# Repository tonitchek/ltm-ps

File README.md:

ltm-ps
======
Power Supply board based on Linear Technology uModule (LTM).

Contents
========
circuit_board :containing the design of the PCB.
simu          :simulation of the design based on LTSpiceIV

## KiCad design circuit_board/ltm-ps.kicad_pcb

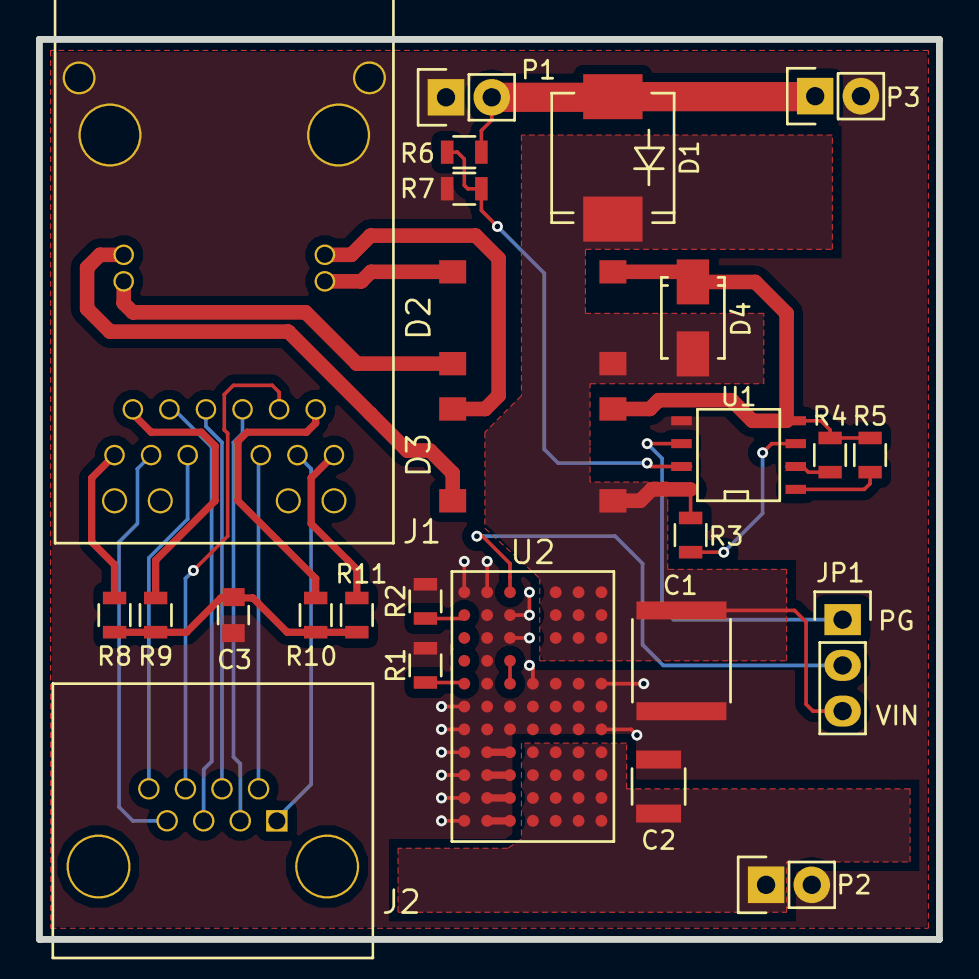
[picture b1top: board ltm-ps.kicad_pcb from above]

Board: 2 copper layers, 50.0 x 50.0 mm, 26 parts (0 on the bottom side), 31 nets.

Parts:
C1: 4.7u; C_2220
C2: 100u; C_1210
C3: 1000p; C_0805
D1: S5BC-13-F; Diode-SMC_Standard
D2, D3: DF01S; SDIP04
D4: SMAJ58CA; Diode-SMA_Standard
J1: 0826-1X1T-M1-F; RJ45_GIGABIT-MAGJACK
J2: RJHSE-5080; RJ45_8N
JP1: JUMPER3; Pin_Header_Straight_1x03
P1, P2, P3: CONN_01X02; Pin_Header_Straight_1x02
R1: 93.1k; R_0805
R2: 90.9k; R_0805
R3: 24.9k; R_0805
R4: 4.42k; R_0805
R5: 178k; R_0805
R6: 150k; R_0805
R7: 100k; R_0805
R8, R9, R10, R11: 75R; R_0805
U1: NCP1092; SOIC-8-N
U2: LTM8050; BGA70-linear_standard

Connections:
/AUX: R6.2, R7.1, U1.7
/TRD1+: J1.11, J2.1
/TRD1-: J1.10, J2.2
/TRD2+: J1.4, J2.3
/TRD2-: J1.5, J2.6
/TRD3+: J1.3, J2.4
/TRD3-: J1.2, J2.5
/TRD4+: J1.8, J2.7
/TRD4-: J1.9, J2.8
/VAUX: D1.1, P1.2, P3.1, R6.1
/VPORT_N: D2.2, D3.2, D4.2, R4.2, R5.2, U1.4
/VPORT_P: C1.1, D1.2, D2.1, D3.1, D4.1, JP1.3, R3.1, U1.8, U2.J1, U2.J2, U2.J3, U2.K1, U2.K2, U2.K3, U2.L1, U2.L2, U2.L3
/VPoE_1+: D2.4, J1.13
/VPoE_1-: D2.3, J1.14
/VPoE_2+: D3.4, J1.15
/VPoE_2-: D3.3, J1.16
/vout_5V@2A: C2.1, P2.1, U2.A1, U2.A2, U2.A3, U2.A4, U2.B1, U2.B2, U2.B3, U2.B4, U2.C1, U2.C2, U2.C3, U2.C4, U2.D1, U2.D2, U2.D3, U2.D4
GND: C1.2, C2.2, C3.2, J1.21, J1.22, J1.23, J1.24, P1.1, P2.2, P3.2, R1.2, R2.2, R7.2, U1.5, U2.A5, U2.A6, U2.A7, U2.B5, U2.B6, U2.B7, U2.C5, U2.C6, U2.C7, U2.D5, U2.D6, U2.D7, U2.E1, U2.E2, U2.E3, U2.E4, U2.E5, U2.E6, U2.E7, U2.F1, U2.F2, U2.F3, U2.F4, U2.F5, U2.F6, U2.F7, U2.G1, U2.G2, U2.G3, U2.G4, U2.G6, U2.H6, U2.J5, U2.J6, U2.K5, U2.K6, U2.L6, U2.L7
unnamed: C3.1, R8.1, R9.1, R10.1, R11.1
unnamed: J1.1, R9.2
unnamed: J1.6, R10.2
unnamed: J1.7, R8.2
unnamed: J1.12, R11.2
unnamed: JP1.1, U1.6
unnamed: JP1.2, U2.L5
unnamed: R1.1, U2.G7
unnamed: R2.1, U2.K7
unnamed: R3.2, U1.3
unnamed: R4.1, U1.2
unnamed: R5.1, U1.1
unnamed: U2.G5, U2.H5

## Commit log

2015-01-19 correct README.md describing tree
2015-01-19 add design and simulation files
2015-01-21 add circuit board design. Start schematic.
2015-01-22 modify simulation schematic
    remove optional compensation loop, change some parameters
2015-01-22 add simulation results report
2015-01-22 change vout and load values
2015-01-22 add diagram of power supply design
2015-01-27 renamed ltm-ps to ltm4609 because a simu based on another ltm will be done
2015-01-27 add simulation of LTM8050
2015-01-28 simulate behavior of ltm8050 at maximum Vin rating voltage
2015-01-28 add simulation of auxiliary source vs PoE voltage behavior
2015-01-28 restart schamatic based on PoE feature with LTM8050 step-down converter
2015-01-29 add PoE front end stage simulation
2015-01-29 add main IC in library and schematics
2015-02-02 remove cache files
2015-02-02 add LTM800 and NCP1092 ICs settings components. Miss RJ45 with magnetics connector
2015-02-02 tie ltm8050 sync pin to ground and refactor ncp1092 to diode rectifiers cabling
2015-02-02 add schematic comments and wire jumper
2015-02-02 check ERC rules
2015-02-02 add ncp1092 resistors settings comments
2015-02-03 add RJ45 PoE component in schematic
2015-02-03 save project file
2015-02-04 add RJ45 out connector and some comments
2015-02-04 perform ERC check on schematic
2015-02-04 add netlist file
2015-02-04 create component to footprint association
2015-02-04 add pcbnew libraries in project files
2015-02-10 create schematic netlist, component to footprint association and BOM
2015-02-11 replace RJ45 output component and change some footprints association
2015-02-11 update footprint association of DF01S component
2015-02-11 add pcb design. Component/Footprint imported from netlist
2015-02-18 start to place component in pcb
2015-02-18 change feedback resistor value to fit value available in components providers
2015-02-19 placing ltm8050 and diode rectifiers
2015-03-13 routed all tracks. Miss gnd plane and check
2015-03-23 review design: correct inverting RJ45 signals. Modify ltm feedback resistor from 89.4k to 90.9k. Add silkscreen text for jumper
2015-03-23 add BOM file
2015-04-10 update BOM due to providers components availibilities
2015-04-26 add dc-dc library in project
